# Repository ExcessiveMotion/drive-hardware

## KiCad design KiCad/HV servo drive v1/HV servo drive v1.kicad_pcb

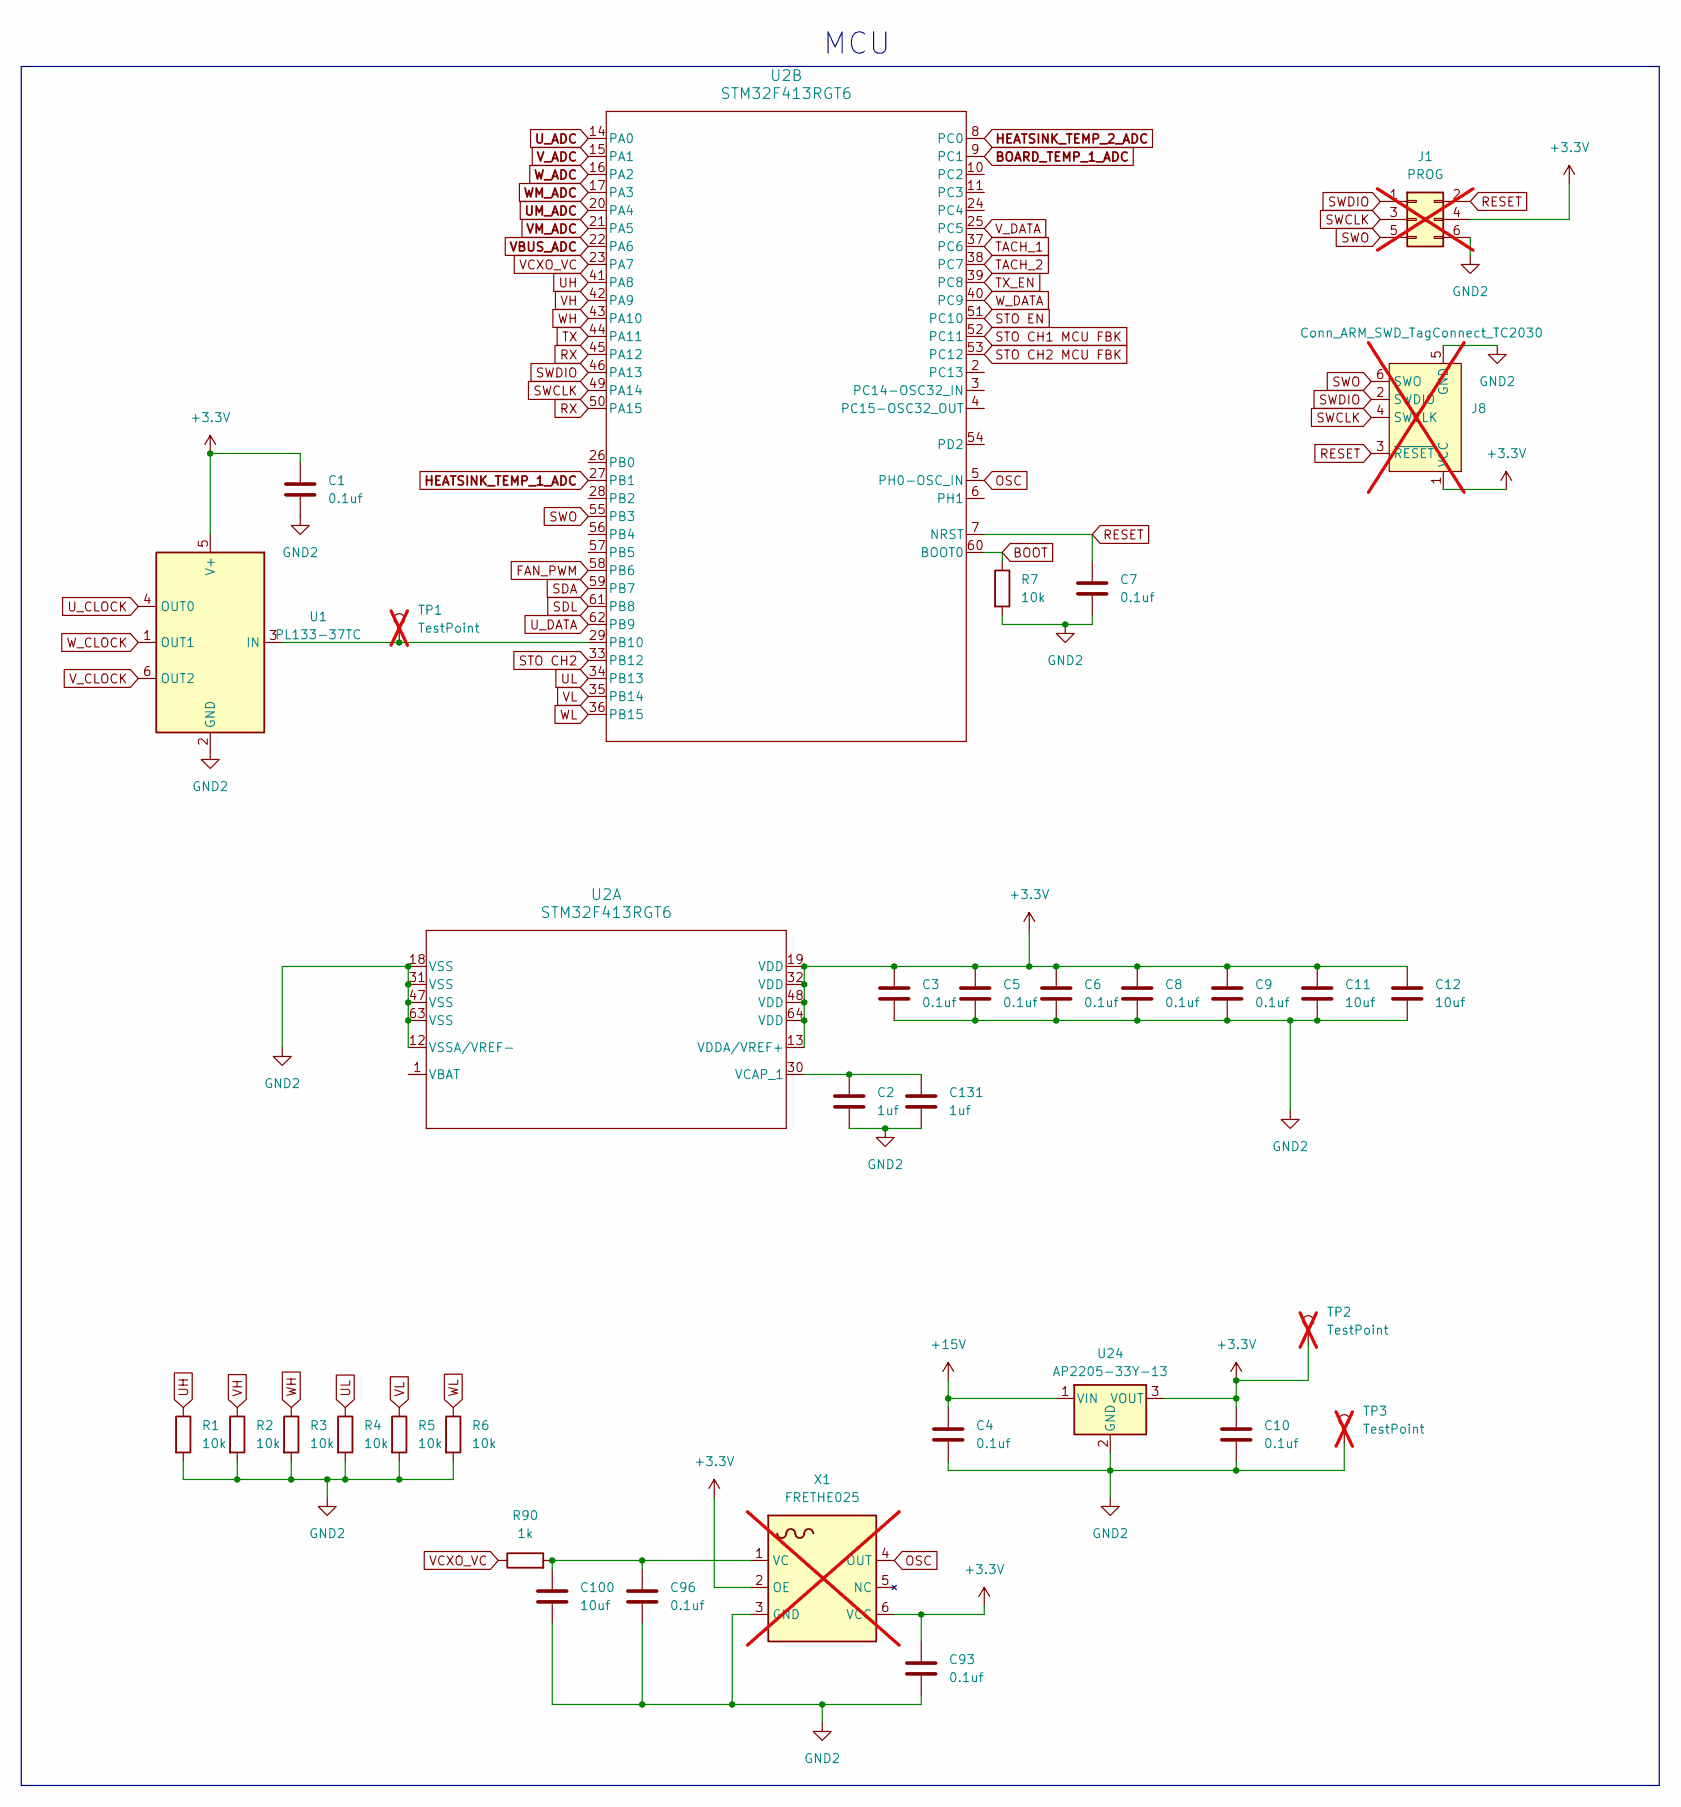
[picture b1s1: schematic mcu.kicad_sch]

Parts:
C1, C3, C4, C5, C6, C7, C8, C9, C10, C93, C96: 0.1uf; C_0603_1608Metric; Part number CC0603ZRY5V9BB104
C2, C131: 1uf; C_0603_1608Metric; Part number CL10A105KB8NNNC
C11, C12, C100: 10uf; C_0805_2012Metric; Part number GRM21BR61H106KE43L
J1: PROG; PinHeader_2x03_P2.54mm_Vertical; not fitted
J8: Conn_ARM_SWD_TagConnect_TC2030; Tag-Connect_TC2030-IDC-FP_2x03_P1.27mm_Vertical; not fitted
R1, R2, R3, R4, R5, R6, R7: 10k; R_0603_1608Metric; Part number RC0603FR-0710KL
R90: 1k; R_0603_1608Metric; Part number RC0603FR-071KL
TP1, TP2, TP3: TestPoint; TestPoint_Pad_3.1x1.6mm; not fitted
U1: PL133-37TC; SOT-23-6; Part number PL133-37TC
U2: STM32F413RGT6; LQFP64-10x10mm; Part number STM32F413RGT6
U24: AP2205-33Y-13; SOT-89-3; Part number AP2205-33Y-13
X1: FRETHE025; FR_3-3V; Part number FRETHE025; not fitted

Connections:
+3.3V: C1.1, C3.1, C5.1, C6.1, C8.1, C9.1, C10.1, C11.1, C12.1, C93.1, J1.4, J8.1 (VCC), TP2.1, U1.5 (V+), U2.13 (VDDA/VREF+), U2.19 (VDD), U2.32 (VDD), U2.48 (VDD), U2.64 (VDD), U24.3 (VOUT), X1.2 (OE), X1.6 (VCC); also elsewhere on the board
+15V: C4.1, U24.1 (VIN); also elsewhere on the board
BOARD_TEMP_1_ADC: U2.9 (PC1); also elsewhere on the board
BOOT: R7.1, U2.60 (BOOT0)
FAN_PWM: U2.58 (PB6); also elsewhere on the board
GND2: C1.2, C2.2, C3.2, C4.2, C5.2, C6.2, C7.2, C8.2, C9.2, C10.2, C11.2, C12.2, C93.2, C96.2, C100.2, C131.2, J1.6, J8.5 (GND), R1.2, R2.2, R3.2, R4.2, R5.2, R6.2, R7.2, TP3.1, U1.2 (GND), U2.12 (VSSA/VREF-), U2.18 (VSS), U2.31 (VSS), U2.47 (VSS), U2.63 (VSS), U24.2 (GND), X1.3 (GND); also elsewhere on the board
HEATSINK_TEMP_1_ADC: U2.27 (PB1); also elsewhere on the board
HEATSINK_TEMP_2_ADC: U2.8 (PC0); also elsewhere on the board
unnamed: TP1.1, U1.3 (IN), U2.29 (PB10)
unnamed: C2.1, C131.1, U2.30 (VCAP_1)
unnamed: C96.1, C100.1, R90.2, X1.1 (VC)
OSC: U2.5 (PH0-OSC_IN), X1.4 (OUT)
RESET: C7.1, J1.2, J8.3 (~RESET), U2.7 (NRST)
RX: U2.45 (PA12), U2.50 (PA15); also elsewhere on the board
SDA: U2.59 (PB7); also elsewhere on the board
SDL: U2.61 (PB8); also elsewhere on the board
STO CH1 MCU FBK: U2.52 (PC11); also elsewhere on the board
STO CH2: U2.33 (PB12); also elsewhere on the board
STO CH2 MCU FBK: U2.53 (PC12); also elsewhere on the board
STO EN: U2.51 (PC10); also elsewhere on the board
SWCLK: J1.3, J8.4 (SWCLK), U2.49 (PA14)
SWDIO: J1.1, J8.2 (SWDIO), U2.46 (PA13)
SWO: J1.5, J8.6 (SWO), U2.55 (PB3)
TACH_1: U2.37 (PC6); also elsewhere on the board
TACH_2: U2.38 (PC7); also elsewhere on the board
TX: U2.44 (PA11); also elsewhere on the board
TX_EN: U2.39 (PC8); also elsewhere on the board
UH: R1.1, U2.41 (PA8); also elsewhere on the board
UL: R4.1, U2.34 (PB13); also elsewhere on the board
UM_ADC: U2.20 (PA4); also elsewhere on the board
U_ADC: U2.14 (PA0); also elsewhere on the board
U_CLOCK: U1.4 (OUT0); also elsewhere on the board
U_DATA: U2.62 (PB9); also elsewhere on the board
VBUS_ADC: U2.22 (PA6); also elsewhere on the board
VCXO_VC: R90.1, U2.23 (PA7)
VH: R2.1, U2.42 (PA9); also elsewhere on the board
VL: R5.1, U2.35 (PB14); also elsewhere on the board
VM_ADC: U2.21 (PA5); also elsewhere on the board
V_ADC: U2.15 (PA1); also elsewhere on the board
V_CLOCK: U1.6 (OUT2); also elsewhere on the board
V_DATA: U2.25 (PC5); also elsewhere on the board
WH: R3.1, U2.43 (PA10); also elsewhere on the board
WL: R6.1, U2.36 (PB15); also elsewhere on the board
WM_ADC: U2.17 (PA3); also elsewhere on the board
W_ADC: U2.16 (PA2); also elsewhere on the board
W_CLOCK: U1.1 (OUT1); also elsewhere on the board
W_DATA: U2.40 (PC9); also elsewhere on the board

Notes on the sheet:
MCU

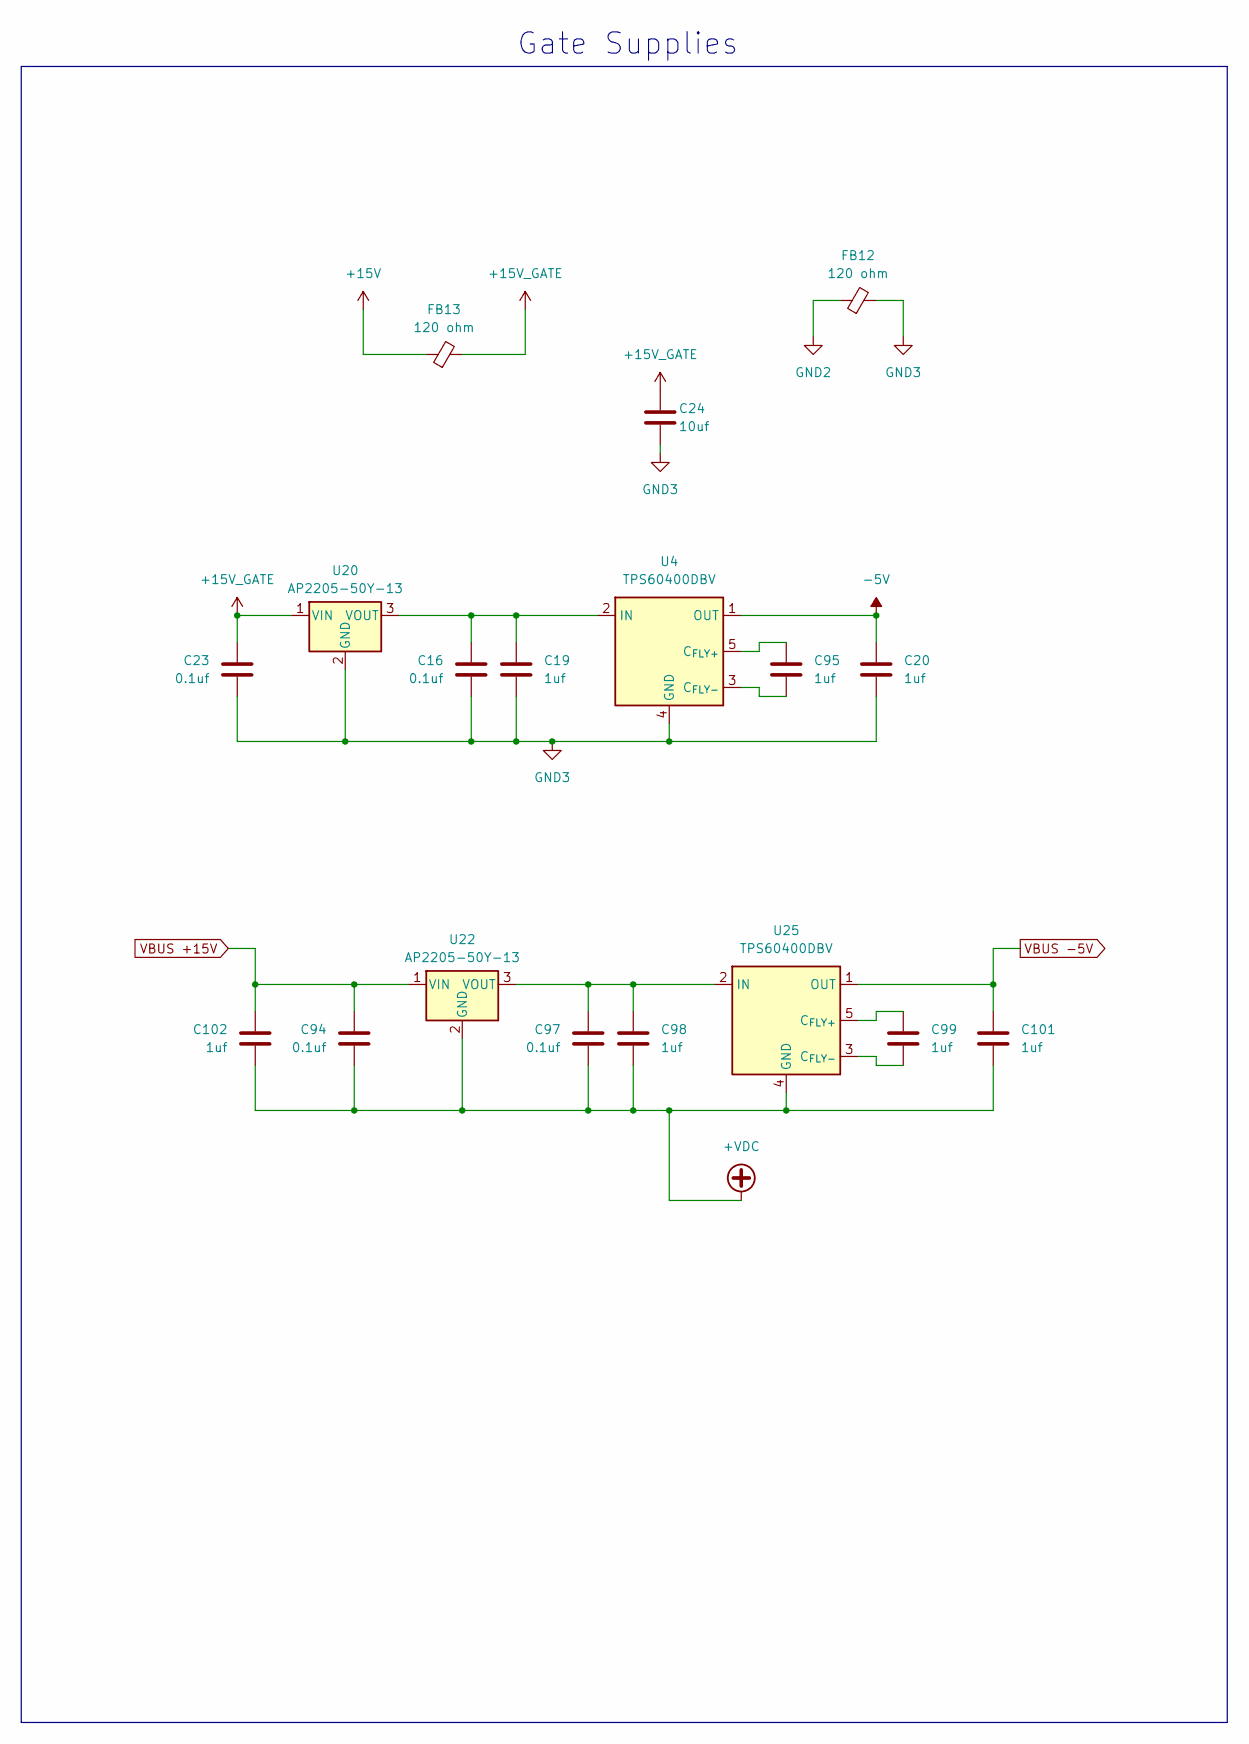
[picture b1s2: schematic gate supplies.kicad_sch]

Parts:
C16, C23, C94, C97: 0.1uf; C_0603_1608Metric; Part number CC0603ZRY5V9BB104
C19, C20, C95, C98, C99, C101, C102: 1uf; C_0603_1608Metric; Part number CL10A105KB8NNNC
C24: 10uf; C_0805_2012Metric; Part number GRM21BR61H106KE43L
FB12, FB13: 120 ohm; L_0603_1608Metric; Part number LI0603G121R-10
U4, U25: TPS60400DBV; SOT-23-5; Part number TPS60400DBV
U20, U22: AP2205-50Y-13; SOT-89-3; Part number AP2205-50Y-13

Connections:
+15V: FB13.1; also elsewhere on the board
+15V_GATE: C23.1, C24.1, FB13.2, U20.1 (VIN); also elsewhere on the board
-5V: C20.1, U4.1 (OUT); also elsewhere on the board
DCBUS+: C94.2, C97.2, C98.2, C101.2, C102.2, U22.2 (GND), U25.4 (GND); also elsewhere on the board
GND2: FB12.1; also elsewhere on the board
GND3: C16.2, C19.2, C20.2, C23.2, C24.2, FB12.2, U4.4 (GND), U20.2 (GND); also elsewhere on the board
unnamed: C95.1, U4.5 (C_{FLY+})
unnamed: C95.2, U4.3 (C_{FLY-})
unnamed: C16.1, C19.1, U4.2 (IN), U20.3 (VOUT)
unnamed: C97.1, C98.1, U22.3 (VOUT), U25.2 (IN)
unnamed: C99.1, U25.5 (C_{FLY+})
unnamed: C99.2, U25.3 (C_{FLY-})
VBUS +15V: C94.1, C102.1, U22.1 (VIN); also elsewhere on the board
VBUS -5V: C101.1, U25.1 (OUT); also elsewhere on the board

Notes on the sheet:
Gate Supplies

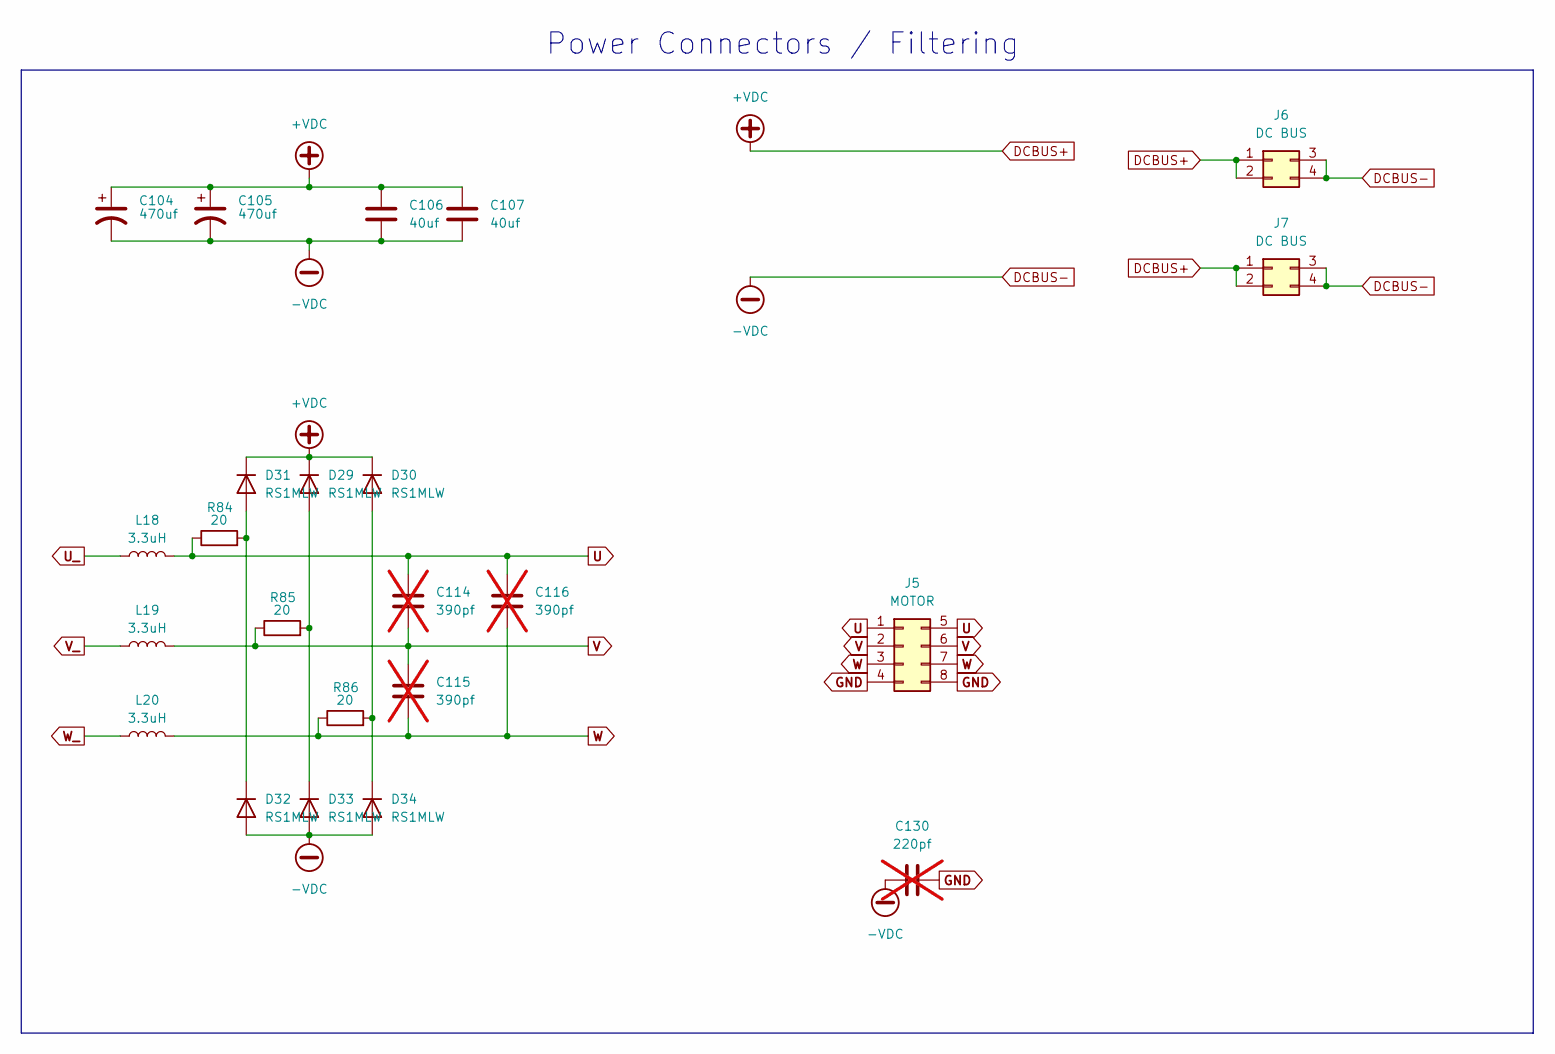
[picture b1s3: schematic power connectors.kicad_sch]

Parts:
C104, C105: 470uf; CP_Radial_D30.0mm_P10.00mm_SnapIn; Part number ESMQ451VSN471MR45S
C106, C107: 40uf; BUS CAP1; Part number C4AQCBW5400A3LJ
C114, C115, C116: 390pf; B326712L-SMD; Part number CC45SL3AD391JYVNA; not fitted
C130: 220pf; C_Disc_D7.5mm_W5.0mm_P10.00mm; Part number DE1B3RA221KN4AP01F; not fitted
D29, D30, D31, D32, D33, D34: RS1MLW; D_SOD-123W; Part number RS1MLW
J5: MOTOR; Molex_Mega-Fit_76825-0008_2x04_P5.70mm_Horizontal; Part number 0768250008
J6, J7: DC BUS; Molex_Mega-Fit_76825-0004_2x02_P5.70mm_Horizontal; Part number 0768250004
L18, L19, L20: 3.3uH; L_Vishay_IHLP-6767; Part number IHLP6767GZER3R3M01
R84, R85, R86: 20; R_1210_3225Metric; Part number CRCW121020R0JNEAHP

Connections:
DCBUS+: C104.1, C105.1, C106.1, C107.1, D29.1 (K), D30.1 (K), D31.1 (K), J6.1, J6.2, J7.1, J7.2; also elsewhere on the board
DCBUS-: C104.2, C105.2, C106.2, C107.2, C130.2, D32.2 (A), D33.2 (A), D34.2 (A), J6.3, J6.4, J7.3, J7.4; also elsewhere on the board
GND: C130.1, J5.4, J5.8; also elsewhere on the board
unnamed: D29.2 (A), D33.1 (K), R85.2
unnamed: D30.2 (A), D34.1 (K), R86.2
unnamed: D31.2 (A), D32.1 (K), R84.2
U: C114.2, C116.1, J5.1, J5.5, L18.2, R84.1; also elsewhere on the board
U_: L18.1; also elsewhere on the board
V: C114.1, C115.2, J5.2, J5.6, L19.2, R85.1; also elsewhere on the board
V_: L19.1; also elsewhere on the board
W: C115.1, C116.2, J5.3, J5.7, L20.2, R86.1; also elsewhere on the board
W_: L20.1; also elsewhere on the board

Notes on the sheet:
Power Connectors / Filtering

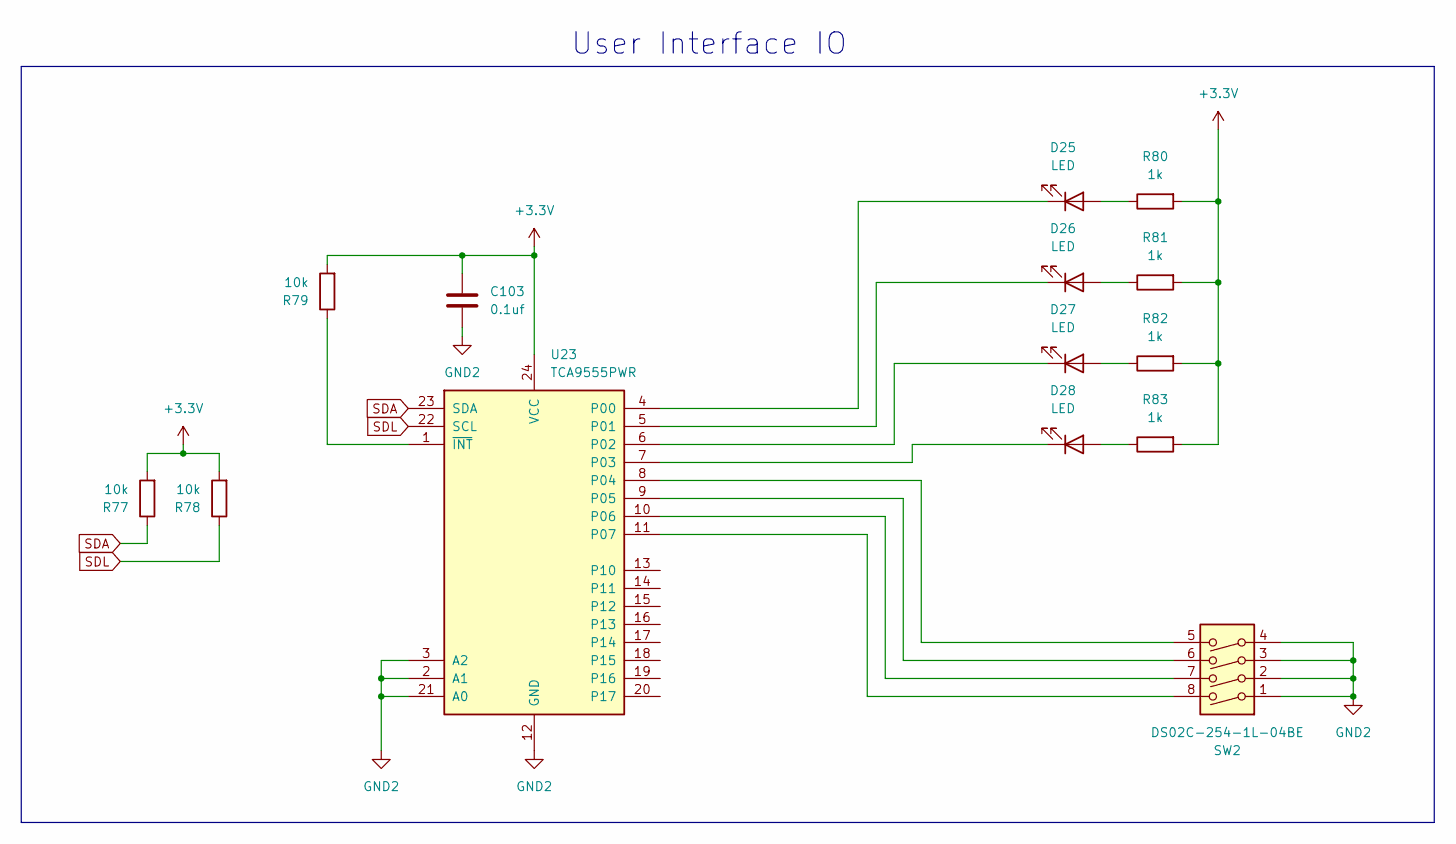
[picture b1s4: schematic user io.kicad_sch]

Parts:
C103: 0.1uf; C_0603_1608Metric; Part number CC0603ZRY5V9BB104
D25, D26, D27, D28: LED; LED_0603_1608Metric; Part number B1931NG--20D001114U1930
R77, R78, R79: 10k; R_0603_1608Metric; Part number RC0603FR-0710KL
R80, R81, R82, R83: 1k; R_0603_1608Metric; Part number RC0603FR-071KL
SW2: DS02C-254-1L-04BE; DIP-8_W7.62mm; Part number DS02C-254-1L-04BE
U23: TCA9555PWR; TSSOP-24_4.4x7.8mm_P0.65mm; Part number TCA9555PWR

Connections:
+3.3V: C103.1, R77.2, R78.2, R79.2, R80.2, R81.2, R82.2, R83.2, U23.24 (VCC); also elsewhere on the board
GND2: C103.2, SW2.1, SW2.2, SW2.3, SW2.4, U23.2 (A1), U23.3 (A2), U23.12 (GND), U23.21 (A0); also elsewhere on the board
unnamed: D25.2 (A), R80.1
unnamed: D25.1 (K), U23.4 (P00)
unnamed: D26.2 (A), R81.1
unnamed: D26.1 (K), U23.5 (P01)
unnamed: D27.2 (A), R82.1
unnamed: D27.1 (K), U23.6 (P02)
unnamed: D28.2 (A), R83.1
unnamed: D28.1 (K), U23.7 (P03)
unnamed: SW2.5, U23.8 (P04)
unnamed: SW2.6, U23.9 (P05)
unnamed: SW2.7, U23.10 (P06)
unnamed: SW2.8, U23.11 (P07)
unnamed: R79.1, U23.1 (~INT)
SDA: R77.1, U23.23 (SDA); also elsewhere on the board
SDL: R78.1, U23.22 (SCL); also elsewhere on the board

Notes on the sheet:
User Interface IO

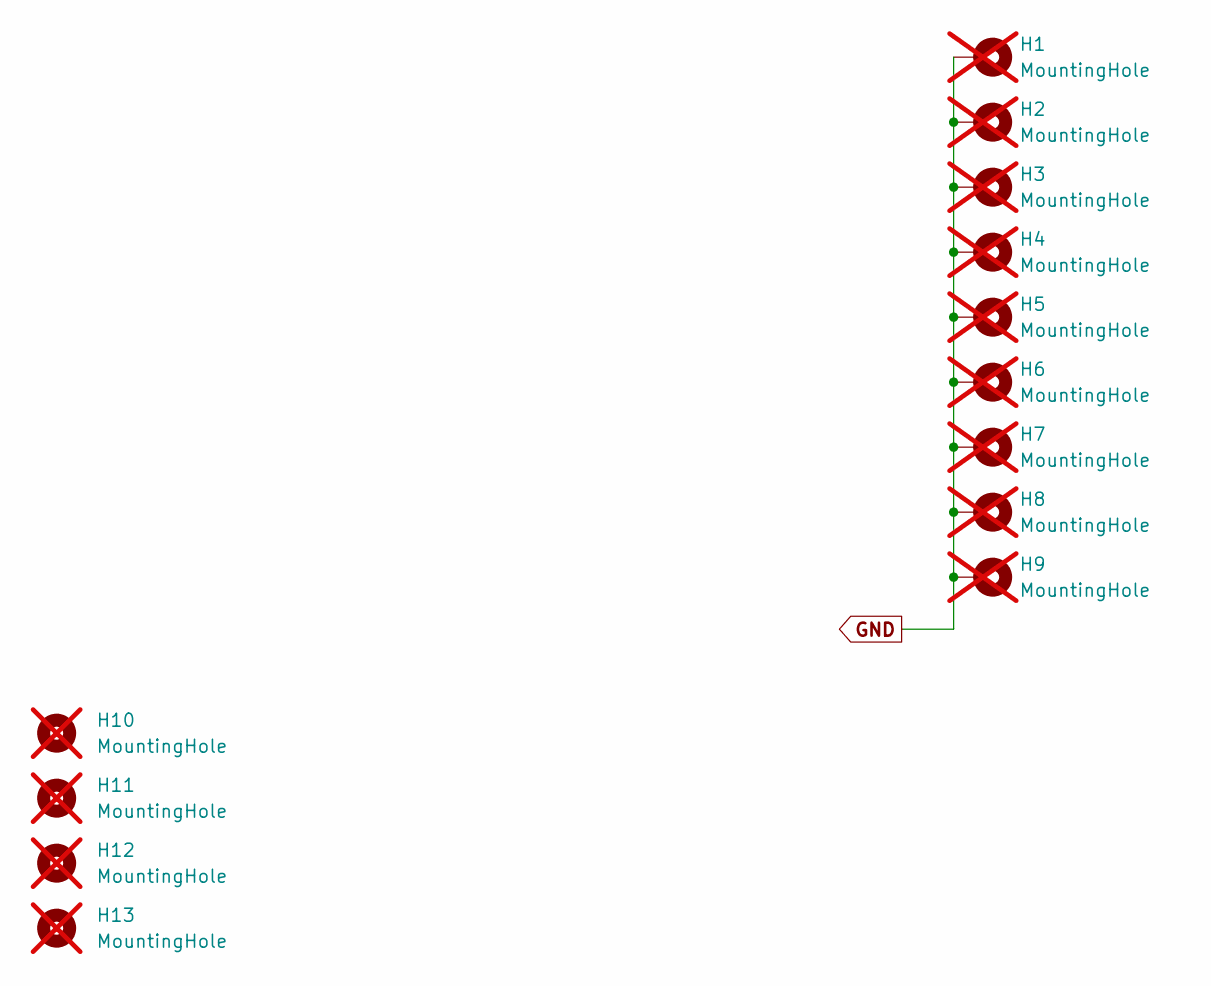
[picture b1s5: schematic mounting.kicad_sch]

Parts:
H1, H2, H3, H4, H5, H6, H7, H8, H9, H10, H11, H12, H13: MountingHole; MountingHole_3.2mm_M3_Pad_TopBottom_LargeIsolation; not fitted

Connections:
GND: H1.1, H2.1, H3.1, H4.1, H5.1, H6.1, H7.1, H8.1, H9.1; also elsewhere on the board

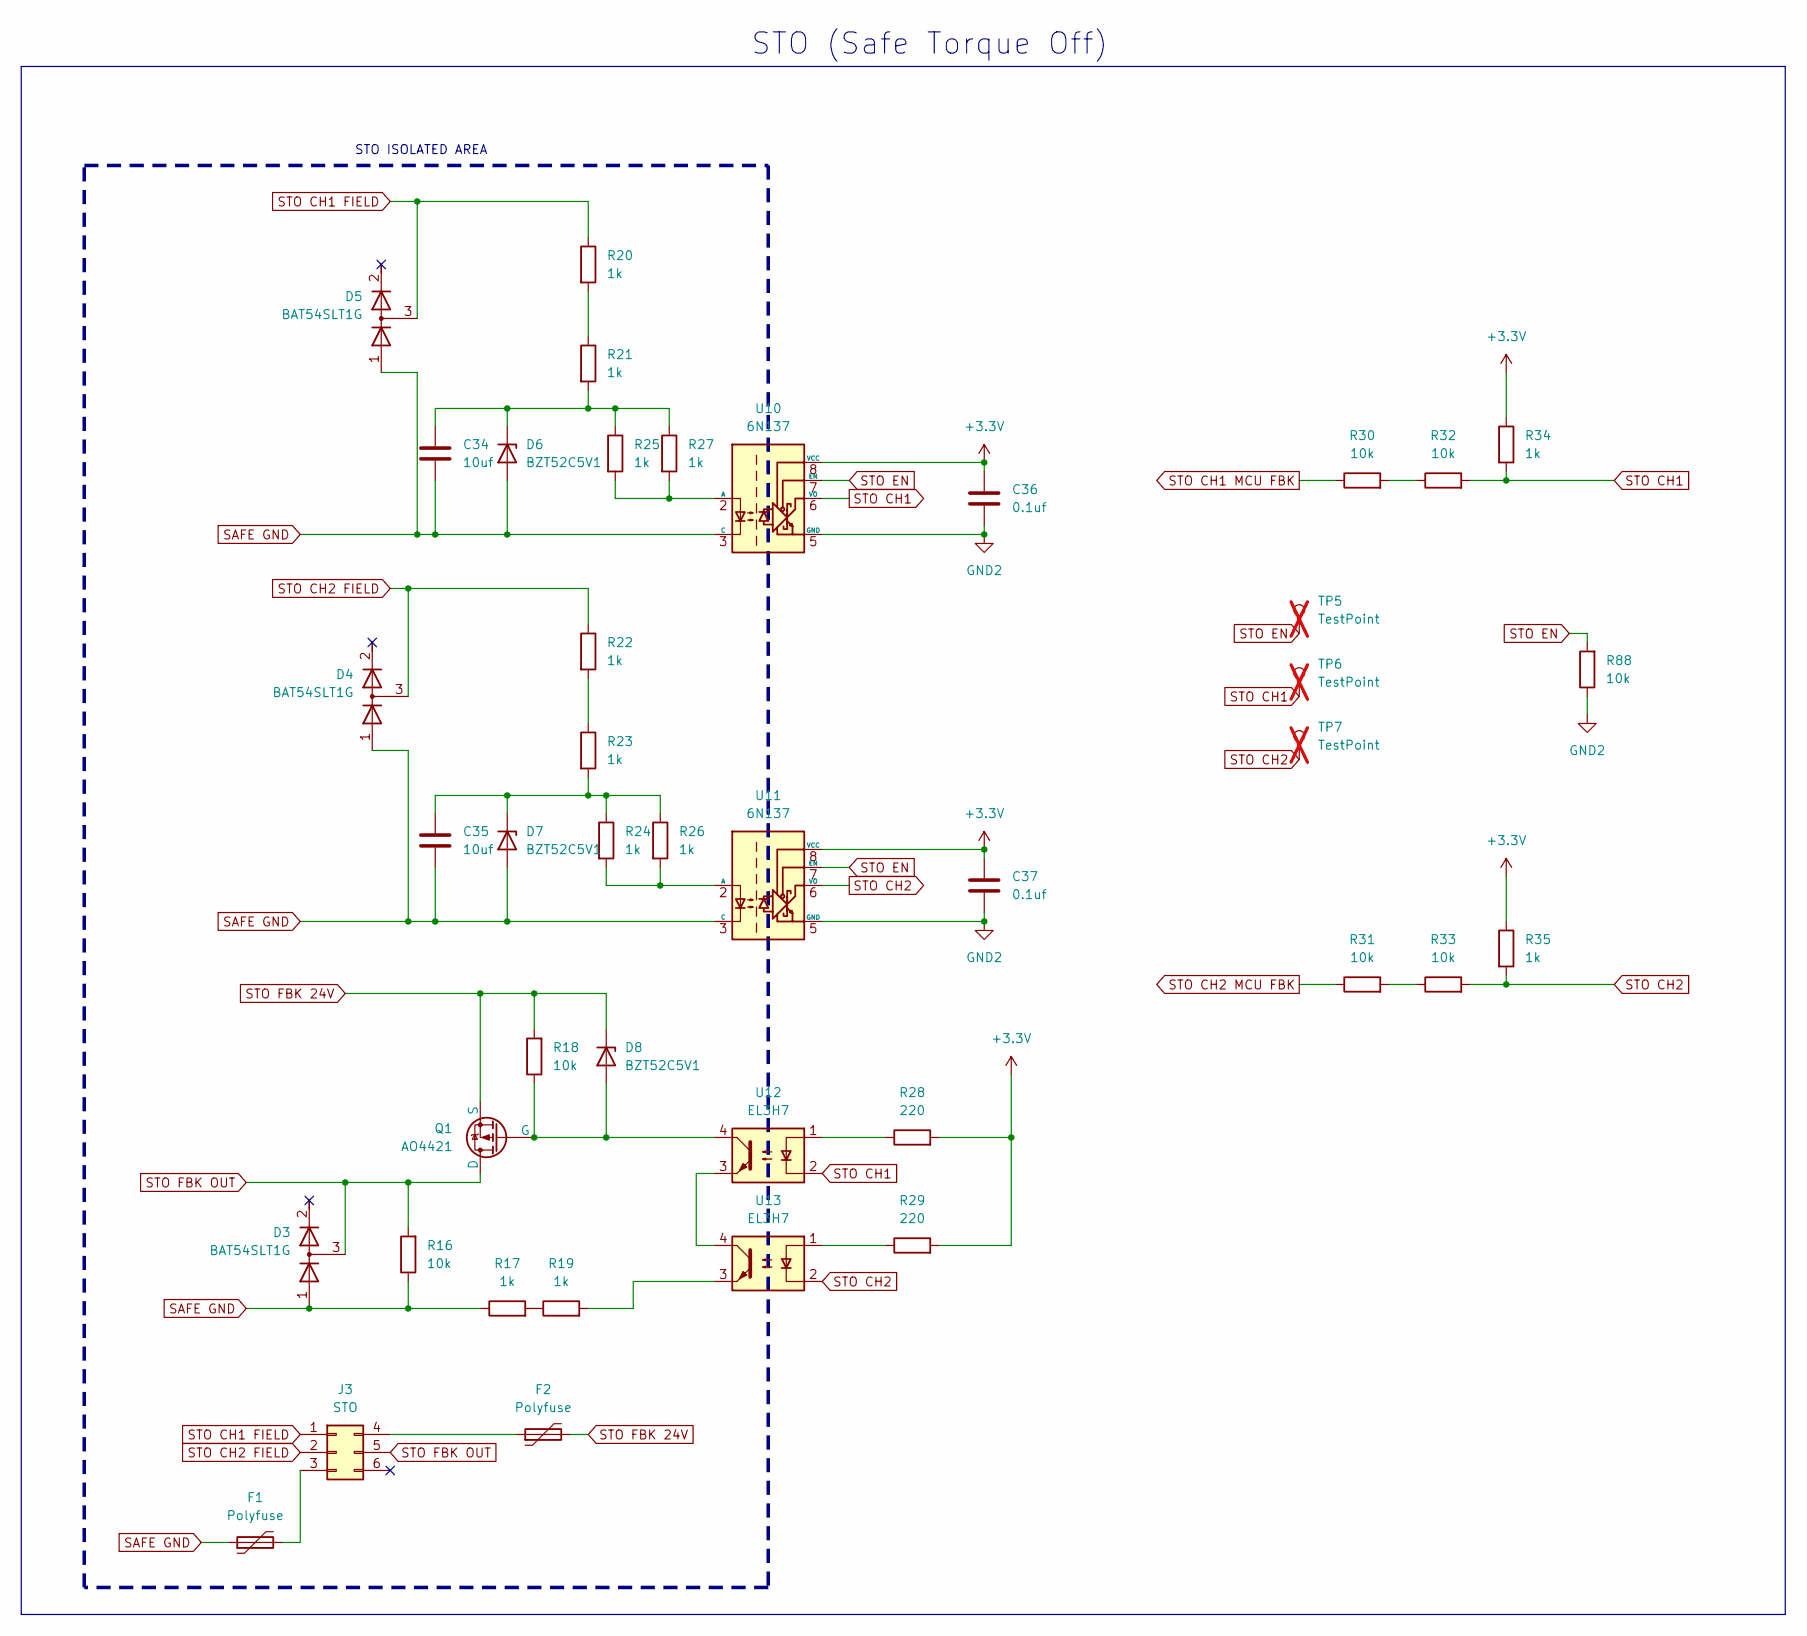
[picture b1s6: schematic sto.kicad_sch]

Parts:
C34, C35: 10uf; C_0805_2012Metric; Part number GRM21BR61H106KE43L
C36, C37: 0.1uf; C_0603_1608Metric; Part number CC0603ZRY5V9BB104
D3, D4, D5: BAT54SLT1G; SOT-23; Part number BAT54SLT1G
D6, D7, D8: BZT52C5V1; D_SOD-123; Part number BZT52C5V1-TP
F1, F2: Polyfuse; Fuse_1206_3216Metric; Part number PTS120660V005
J3: STO; Molex_Mini-Fit_Jr_0455580003_2x03_P4.20mm_Horizontal; Part number 0455580003
Q1: AO4421; SOIC-8_3.9x4.9mm_P1.27mm; Part number AO4421
R16, R18, R30, R31, R32, R33, R88: 10k; R_0603_1608Metric; Part number RC0603FR-0710KL
R17, R19, R20, R21, R22, R23, R24, R25, R26, R27, R34, R35: 1k; R_0603_1608Metric; Part number RC0603FR-071KL
R28, R29: 220; R_0603_1608Metric; Part number RC0603FR-07220RL
TP5, TP6, TP7: TestPoint; TestPoint_Pad_3.1x1.6mm; not fitted
U10, U11: 6N137; 6N137S_LTO; Part number 6N137S-TA1
U12, U13: EL3H7; SOP-4_4.4x2.6mm_P1.27mm; Part number EL3H7(B)(TA)-VG

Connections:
+3.3V: C36.1, C37.1, R28.2, R29.2, R34.1, R35.1, U10.8 (VCC), U11.8 (VCC); also elsewhere on the board
GND2: C36.2, C37.2, R88.1, U10.5 (GND), U11.5 (GND); also elsewhere on the board
unnamed: C34.1, D6.1 (K), R21.2, R25.1, R27.1
unnamed: C35.1, D7.1 (K), R23.2, R24.1, R26.1
unnamed: D8.2 (A), Q1.4 (G), R18.1, U12.4
unnamed: F1.2, J3.3
unnamed: F2.1, J3.4
unnamed: R17.2, R19.1
unnamed: R19.2, U13.3
unnamed: R20.2, R21.1
unnamed: R22.2, R23.1
unnamed: R28.1, U12.1
unnamed: R29.1, U13.1
unnamed: R30.2, R32.1
unnamed: R31.2, R33.1
unnamed: R25.2, R27.2, U10.2 (A)
unnamed: R24.2, R26.2, U11.2 (A)
unnamed: U12.3, U13.4
SAFE GND: C34.2, C35.2, D3.1 (A), D4.1 (A), D5.1 (A), D6.2 (A), D7.2 (A), F1.1, R16.1, R17.1, U10.3 (C), U11.3 (C)
STO CH1: R32.2, R34.2, TP6.1, U10.6 (VO), U12.2; also elsewhere on the board
STO CH1 FIELD: D5.3 (common), J3.1, R20.1
STO CH1 MCU FBK: R30.1; also elsewhere on the board
STO CH2: R33.2, R35.2, TP7.1, U11.6 (VO), U13.2; also elsewhere on the board
STO CH2 FIELD: D4.3 (common), J3.2, R22.1
STO CH2 MCU FBK: R31.1; also elsewhere on the board
STO EN: R88.2, TP5.1, U10.7 (EN), U11.7 (EN); also elsewhere on the board
STO FBK 24V: D8.1 (K), F2.2, Q1.1 (S), Q1.2 (S), Q1.3 (S), R18.2
STO FBK OUT: D3.3 (common), J3.5, Q1.5 (D), Q1.6 (D), Q1.7 (D), Q1.8 (D), R16.2

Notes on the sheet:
STO (Safe Torque Off)
STO ISOLATED AREA
